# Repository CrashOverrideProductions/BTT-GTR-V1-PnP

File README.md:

# BTT-GTR-V1-PnP  

### **Project**: Pick and Place Expansion Board For BIGTREETECH GTR V1.0

<!-- Repo Cover Image -->

<!-- Repo Stats -->

<!-- Repo Intro -->
### Details
The Goal of this Project is to Create an Expansion Board for the BIGTREETECH 32-Bit 3D Printer Mainboard that includes Functionallity for Pick and Place Machines

<!-- To Do List -->
### Project To Do List
- [X] Design Expansion Board
- [X] Import Marlin
- [X] Import Modified Marlin for PnP (https://github.com/sphawes/index)
- [ ] Create Marlin Board Definition
- [ ] Define RS-485 Communications

### Expansion Board To Do List
- [X] USB Hub
- [X] Vaccuum Sensors
- [X] RS-485
- [ ] More to Add I'm Sure

<!-- Licencing Always at the Bottom -->
### Licencing 

**Creative Commons: Attribution - NonCommercial - ShareAlike 4.0 International (CC BY-NC-SA 4.0)**

**You are free to:**
**Share** — copy and redistribute the material in any medium or format
**Adapt** — remix, transform, and build upon the material

**Under the following terms:**
**Attribution** — You must give appropriate credit, provide a link to the license, and indicate if changes were made. You may do so in any reasonable manner, but not in any way that suggests the licensor endorses you or your use.

**NonCommercial** — You may not use the material for commercial purposes.

**ShareAlike** — If you remix, transform, or build upon the material, you must distribute your contributions under the same license as the original.

No additional restrictions — You may not apply legal terms or technological measures that legally restrict others from doing anything the license permits.

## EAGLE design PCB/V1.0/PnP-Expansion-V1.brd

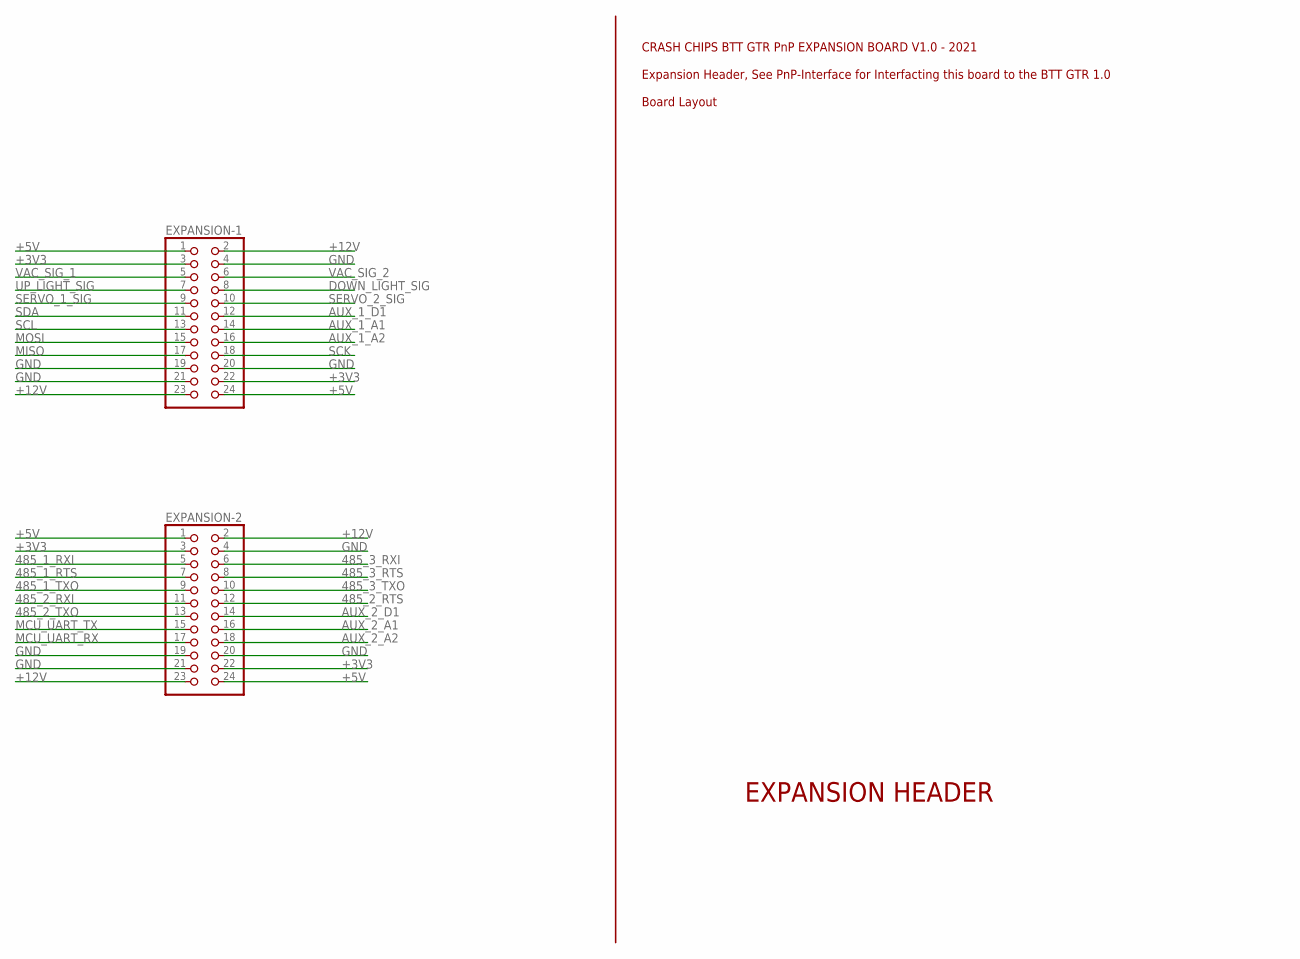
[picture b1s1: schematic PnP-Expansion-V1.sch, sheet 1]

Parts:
EXPANSION-1, EXPANSION-2: PINHD-2X12; 2X12

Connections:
485_1_RTS: EXPANSION-2.7; also elsewhere on the board
485_1_RXI: EXPANSION-2.5; also elsewhere on the board
485_1_TXO: EXPANSION-2.9; also elsewhere on the board
485_2_RTS: EXPANSION-2.12; also elsewhere on the board
485_2_RXI: EXPANSION-2.11; also elsewhere on the board
485_2_TXO: EXPANSION-2.13; also elsewhere on the board
485_3_RTS: EXPANSION-2.8; also elsewhere on the board
485_3_RXI: EXPANSION-2.6; also elsewhere on the board
485_3_TXO: EXPANSION-2.10; also elsewhere on the board
+3V3: EXPANSION-1.3, EXPANSION-1.22, EXPANSION-2.3, EXPANSION-2.22; also elsewhere on the board
+5V: EXPANSION-1.1, EXPANSION-1.24, EXPANSION-2.1, EXPANSION-2.24; also elsewhere on the board
+12V: EXPANSION-1.2, EXPANSION-1.23, EXPANSION-2.2, EXPANSION-2.23; also elsewhere on the board
AUX_1_A1: EXPANSION-1.14; also elsewhere on the board
AUX_1_A2: EXPANSION-1.16; also elsewhere on the board
AUX_1_D1: EXPANSION-1.12; also elsewhere on the board
AUX_2_A1: EXPANSION-2.16; also elsewhere on the board
AUX_2_A2: EXPANSION-2.18; also elsewhere on the board
AUX_2_D1: EXPANSION-2.14; also elsewhere on the board
DOWN_LIGHT_SIG: EXPANSION-1.8; also elsewhere on the board
GND: EXPANSION-1.4, EXPANSION-1.19, EXPANSION-1.20, EXPANSION-1.21, EXPANSION-2.4, EXPANSION-2.19, EXPANSION-2.20, EXPANSION-2.21; also elsewhere on the board
MCU_UART_RX: EXPANSION-2.17; also elsewhere on the board
MCU_UART_TX: EXPANSION-2.15; also elsewhere on the board
MISO: EXPANSION-1.17; also elsewhere on the board
MOSI: EXPANSION-1.15; also elsewhere on the board
SCK: EXPANSION-1.18; also elsewhere on the board
SCL: EXPANSION-1.13; also elsewhere on the board
SDA: EXPANSION-1.11; also elsewhere on the board
SERVO_1_SIG: EXPANSION-1.9; also elsewhere on the board
SERVO_2_SIG: EXPANSION-1.10; also elsewhere on the board
UP_LIGHT_SIG: EXPANSION-1.7; also elsewhere on the board
VAC_SIG_1: EXPANSION-1.5; also elsewhere on the board
VAC_SIG_2: EXPANSION-1.6; also elsewhere on the board

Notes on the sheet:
EXPANSION HEADER
CRASH CHIPS BTT GTR PnP EXPANSION BOARD V1.0 - 2021 Expansion Header, See PnP-Interface for Interfacting this board to the BTT GTR 1.0 Board Layout

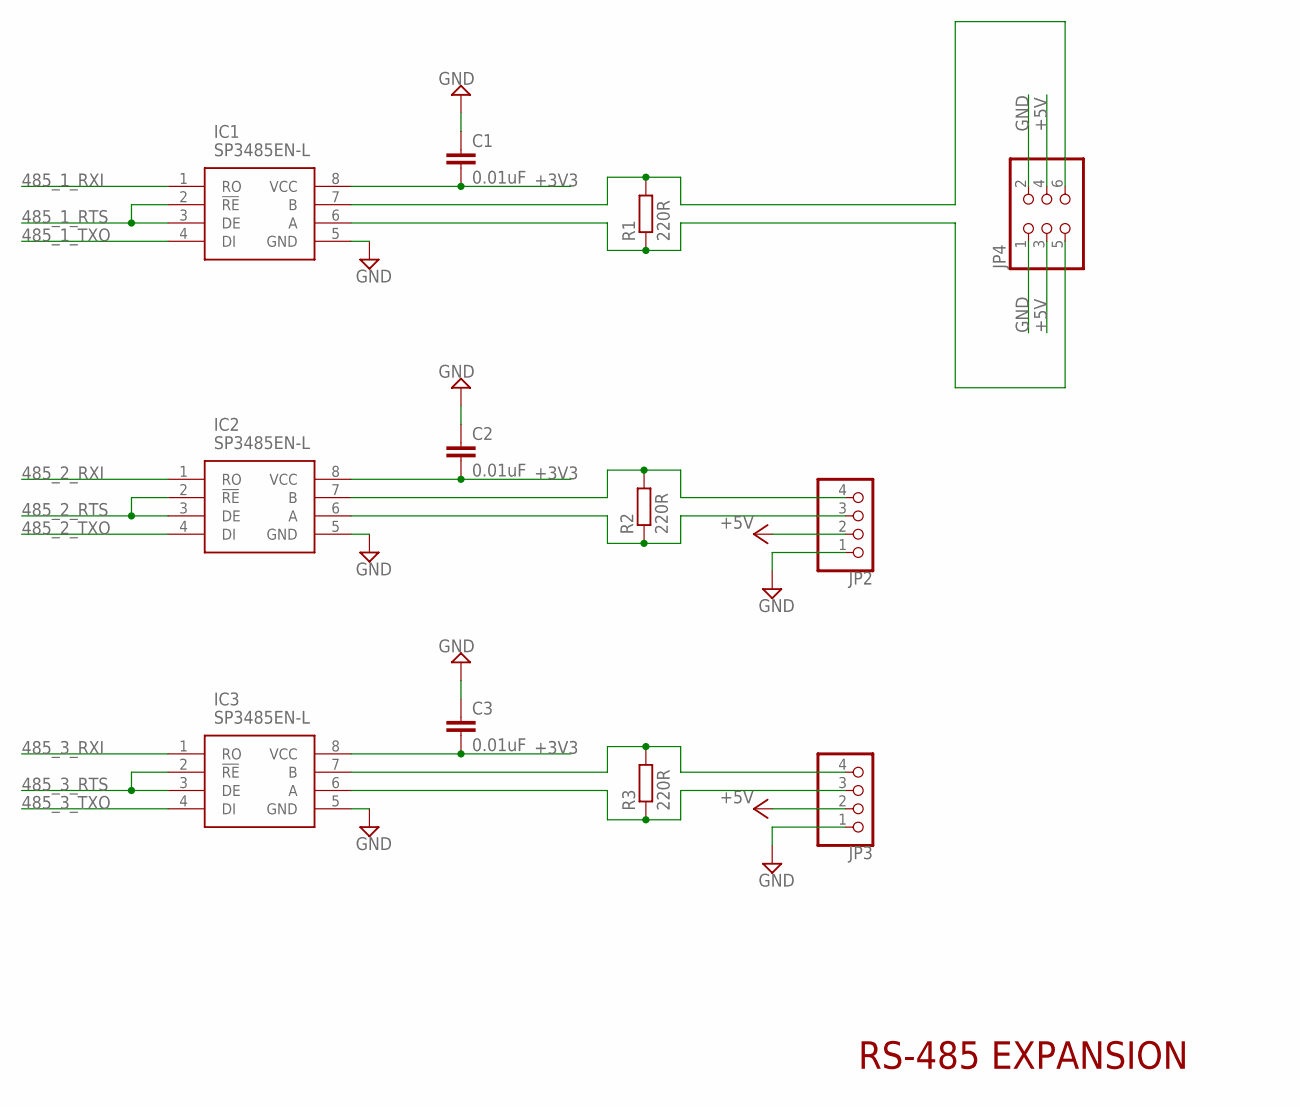
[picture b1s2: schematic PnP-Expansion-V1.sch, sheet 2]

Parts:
C1, C2, C3: 0.01uF; C0805
IC1, IC2, IC3: SP3485EN-L; SOIC127P600X175-8N
JP2, JP3: PINHD-1X4; 1X04
JP4: PINHD-2X3; 2X03
R1, R2, R3: 220R; M0805

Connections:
485_1_RTS: IC1.2 (!RE), IC1.3 (DE); also elsewhere on the board
485_1_RXI: IC1.1 (RO); also elsewhere on the board
485_1_TXO: IC1.4 (DI); also elsewhere on the board
485_2_RTS: IC2.2 (!RE), IC2.3 (DE); also elsewhere on the board
485_2_RXI: IC2.1 (RO); also elsewhere on the board
485_2_TXO: IC2.4 (DI); also elsewhere on the board
485_3_RTS: IC3.2 (!RE), IC3.3 (DE); also elsewhere on the board
485_3_RXI: IC3.1 (RO); also elsewhere on the board
485_3_TXO: IC3.4 (DI); also elsewhere on the board
+3V3: C1.2, C2.2, C3.2, IC1.8 (VCC), IC2.8 (VCC), IC3.8 (VCC); also elsewhere on the board
+5V: JP2.2, JP3.2, JP4.3, JP4.4; also elsewhere on the board
GND: C1.1, C2.1, C3.1, IC1.5 (GND), IC2.5 (GND), IC3.5 (GND), JP2.1, JP3.1, JP4.1, JP4.2; also elsewhere on the board
unnamed: IC3.7 (B), JP3.4, R3.2
unnamed: IC3.6 (A), JP3.3, R3.1
unnamed: IC2.6 (A), JP2.3, R2.1
unnamed: IC2.7 (B), JP2.4, R2.2
unnamed: IC1.6 (A), JP4.5, R1.1
unnamed: IC1.7 (B), JP4.6, R1.2

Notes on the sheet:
RS-485 EXPANSION

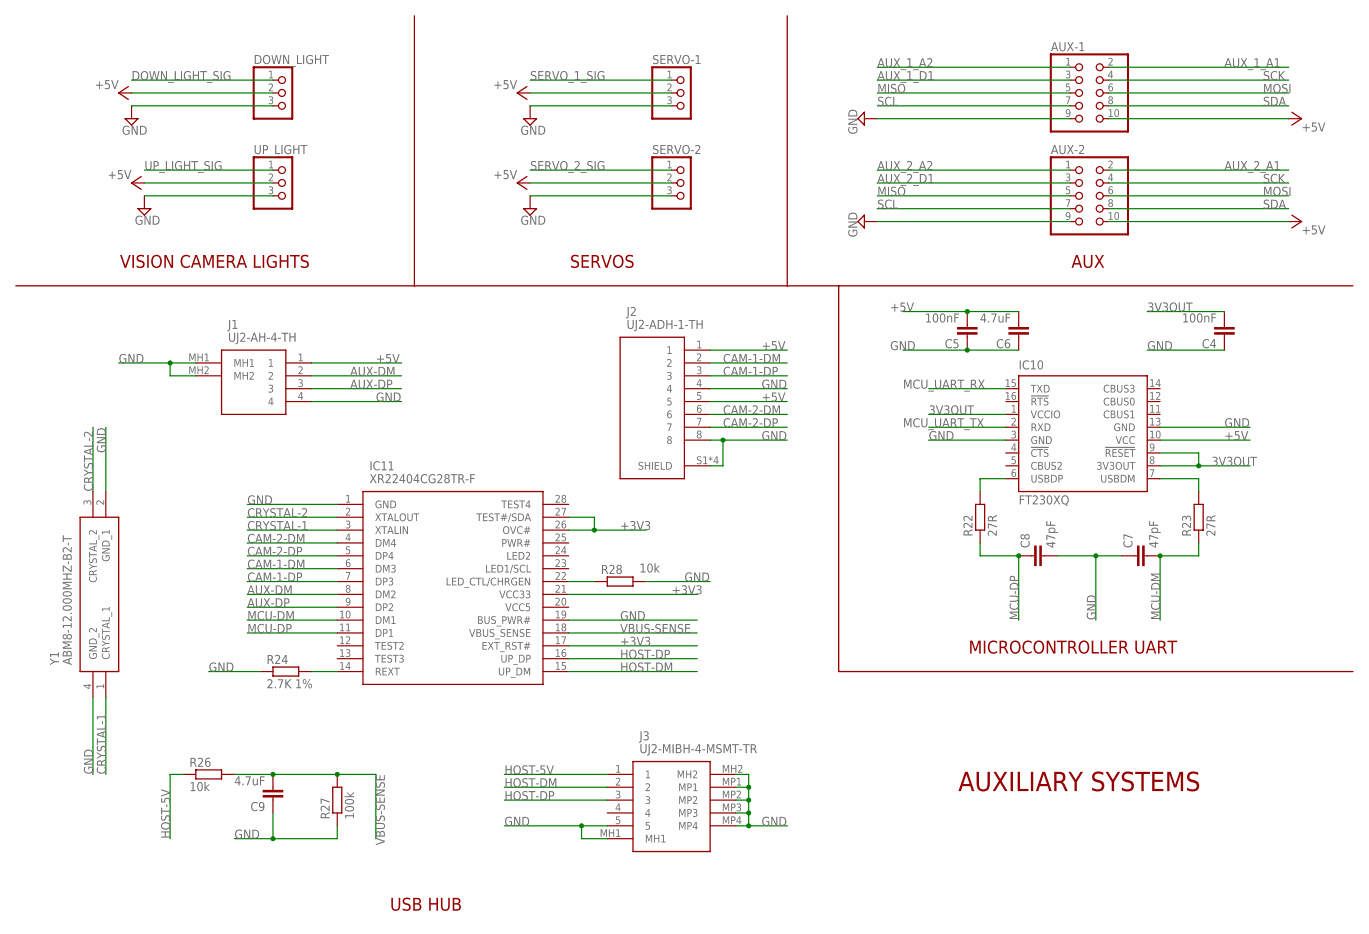
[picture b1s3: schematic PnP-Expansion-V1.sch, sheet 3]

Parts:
AUX-1, AUX-2: PINHD-2X5; 2X05
C4, C5: 100nF; C0805
C6, C9: 4.7uF; C0805
C7, C8: 47pF; C0805
DOWN_LIGHT: PINHD-1X3; 1X03
IC10: FT230XQ; QFN16
IC11: XR22404CG28TR-F; SOP64P600X173-28N
J1: UJ2-AH-4-TH; UJ2AH4TH
J2: UJ2-ADH-1-TH; CUI_UJ2-ADH-1-TH
J3: UJ2-MIBH-4-MSMT-TR; UJ2MIBH4MSMTTR
R22, R23: 27R; M0805
R24: 2.7K 1%; M0805
R26, R28: 10k; M0805
R27: 100k; M0805
SERVO-1, SERVO-2: PINHD-1X3; 1X03
UP_LIGHT: PINHD-1X3; 1X03
Y1: ABM8-12.000MHZ-B2-T; ABM812000MHZB2T

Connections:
3V3OUT: C4.1, IC10.1 (VCCIO), IC10.8 (3V3OUT), IC10.9 (!RESET)
+3V3: IC11.17 (EXT_RST#), IC11.21 (VCC33), IC11.26 (OVC#), IC11.27 (TEST#/SDA); also elsewhere on the board
+5V: AUX-1.10, AUX-2.10, C5.2, C6.2, DOWN_LIGHT.2, IC10.10 (VCC), J1.1, J2.1, J2.5, SERVO-1.2, SERVO-2.2, UP_LIGHT.2; also elsewhere on the board
AUX-DM: IC11.8 (DM2), J1.2
AUX-DP: IC11.9 (DP2), J1.3
AUX_1_A1: AUX-1.2; also elsewhere on the board
AUX_1_A2: AUX-1.1; also elsewhere on the board
AUX_1_D1: AUX-1.3; also elsewhere on the board
AUX_2_A1: AUX-2.2; also elsewhere on the board
AUX_2_A2: AUX-2.1; also elsewhere on the board
AUX_2_D1: AUX-2.3; also elsewhere on the board
CAM-1-DM: IC11.6 (DM3), J2.2
CAM-1-DP: IC11.7 (DP3), J2.3
CAM-2-DM: IC11.4 (DM4), J2.6
CAM-2-DP: IC11.5 (DP4), J2.7
CRYSTAL-1: IC11.3 (XTALIN), Y1.1 (CRYSTAL_1)
CRYSTAL-2: IC11.2 (XTALOUT), Y1.3 (CRYSTAL_2)
DOWN_LIGHT_SIG: DOWN_LIGHT.1; also elsewhere on the board
GND: AUX-1.9, AUX-2.9, C4.2, C5.1, C6.1, C7.1, C8.2, C9.1, DOWN_LIGHT.3, IC10.3 (GND), IC10.13 (GND), IC11.1 (GND), IC11.19 (BUS_PWR#), J1.4, J1.MH1, J1.MH2, J2.4, J2.8, J2.S1 (SHIELD), J2.S2 (SHIELD), J2.S3 (SHIELD), J2.S4 (SHIELD), J3.5, J3.MH1, J3.MH2, J3.MP1, J3.MP2, J3.MP3, J3.MP4, R24.1, R27.1, R28.2, SERVO-1.3, SERVO-2.3, UP_LIGHT.3, Y1.2 (GND_1), Y1.4 (GND_2); also elsewhere on the board
HOST-5V: J3.1, R26.1
HOST-DM: IC11.15 (UP_DM), J3.2
HOST-DP: IC11.16 (UP_DP), J3.3
MCU-DM: C7.2, IC11.10 (DM1), R23.1
MCU-DP: C8.1, IC11.11 (DP1), R22.1
MCU_UART_RX: IC10.15 (TXD); also elsewhere on the board
MCU_UART_TX: IC10.2 (RXD); also elsewhere on the board
MISO: AUX-1.5, AUX-2.5; also elsewhere on the board
MOSI: AUX-1.6, AUX-2.6; also elsewhere on the board
unnamed: IC11.22 (LED_CTL/CHRGEN), R28.1
unnamed: IC10.6 (USBDP), R22.2
unnamed: IC10.7 (USBDM), R23.2
unnamed: IC11.14 (REXT), R24.2
SCK: AUX-1.4, AUX-2.4; also elsewhere on the board
SCL: AUX-1.7, AUX-2.7; also elsewhere on the board
SDA: AUX-1.8, AUX-2.8; also elsewhere on the board
SERVO_1_SIG: SERVO-1.1; also elsewhere on the board
SERVO_2_SIG: SERVO-2.1; also elsewhere on the board
UP_LIGHT_SIG: UP_LIGHT.1; also elsewhere on the board
VBUS-SENSE: C9.2, IC11.18 (VBUS_SENSE), R26.2, R27.2

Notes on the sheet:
AUXILIARY SYSTEMS
VISION CAMERA LIGHTS
SERVOS
AUX
MICROCONTROLLER UART
USB HUB

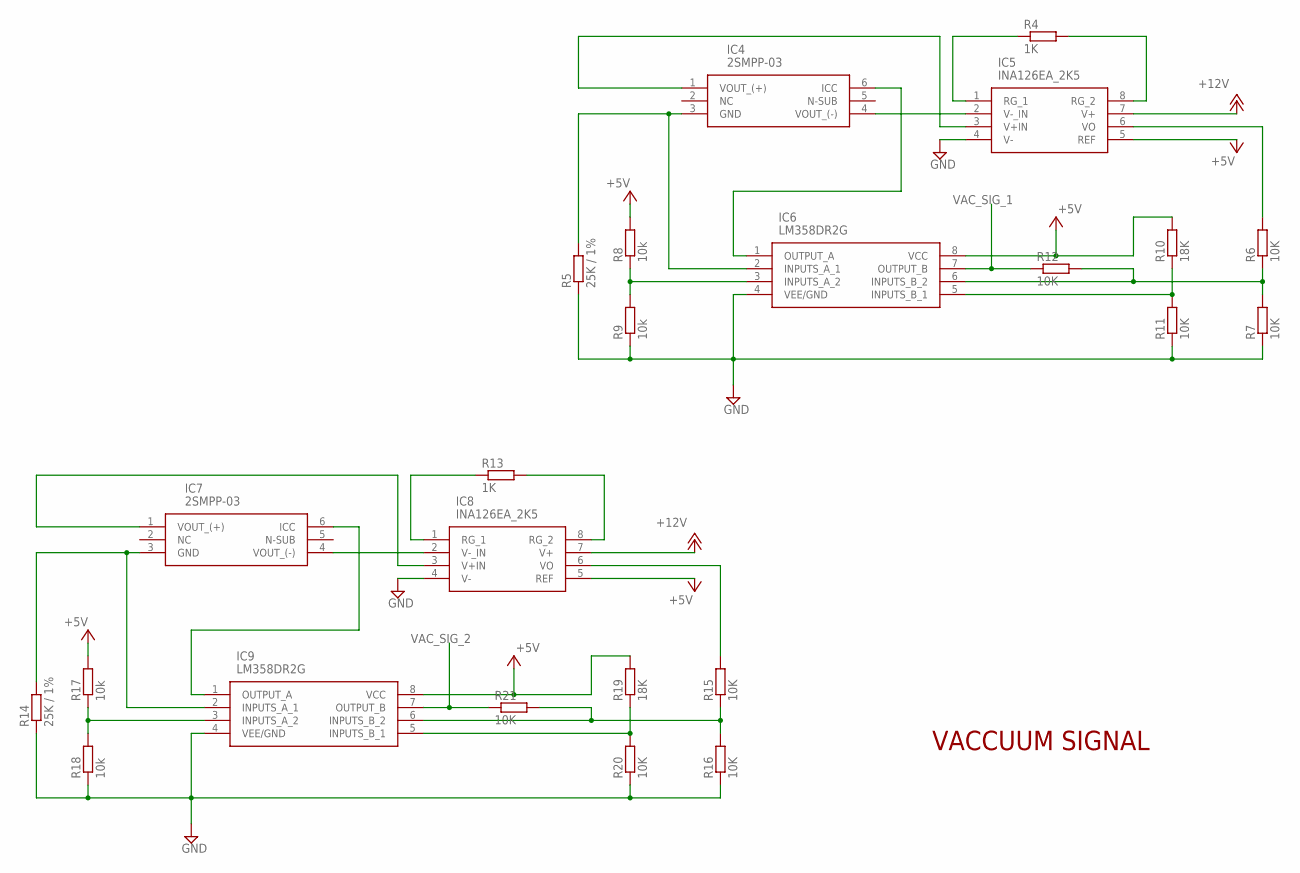
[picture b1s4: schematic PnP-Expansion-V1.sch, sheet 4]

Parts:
IC4, IC7: 2SMPP-03; 2SMPP03
IC5, IC8: INA126EA_2K5; SOP65P490X110-8N
IC6, IC9: LM358DR2G; SOIC127P600X175-8N
R4, R13: 1K; M0805
R5, R14: 25K / 1%; M0805
R6, R7, R11, R12, R15, R16, R20, R21: 10K; M0805
R8, R9, R17, R18: 10k; M0805
R10, R19: 18K; M0805

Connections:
+5V: IC5.5 (REF), IC6.8 (VCC), IC8.5 (REF), IC9.8 (VCC), R8.2, R10.2, R17.2, R19.2; also elsewhere on the board
+12V: IC5.7 (V+), IC8.7 (V+); also elsewhere on the board
GND: IC5.4 (V-), IC6.4 (VEE/GND), IC8.4 (V-), IC9.4 (VEE/GND), R5.1, R7.1, R9.1, R11.1, R14.1, R16.1, R18.1, R20.1; also elsewhere on the board
unnamed: IC4.1 (VOUT_(+)), IC5.3 (V+IN)
unnamed: IC5.1 (RG_1), R4.1
unnamed: IC5.8 (RG_2), R4.2
unnamed: IC4.4 (VOUT_(-)), IC5.2 (V-_IN)
unnamed: IC4.6 (ICC), IC6.1 (OUTPUT_A)
unnamed: IC4.3 (GND), IC6.2 (INPUTS_A_1), R5.2
unnamed: IC6.3 (INPUTS_A_2), R8.1, R9.2
unnamed: IC5.6 (VO), R6.2
unnamed: IC6.6 (INPUTS_B_2), R6.1, R7.2, R12.2
unnamed: IC6.5 (INPUTS_B_1), R10.1, R11.2
unnamed: IC7.1 (VOUT_(+)), IC8.3 (V+IN)
unnamed: IC8.1 (RG_1), R13.1
unnamed: IC8.8 (RG_2), R13.2
unnamed: IC7.4 (VOUT_(-)), IC8.2 (V-_IN)
unnamed: IC7.6 (ICC), IC9.1 (OUTPUT_A)
unnamed: IC7.3 (GND), IC9.2 (INPUTS_A_1), R14.2
unnamed: IC9.3 (INPUTS_A_2), R17.1, R18.2
unnamed: IC8.6 (VO), R15.2
unnamed: IC9.6 (INPUTS_B_2), R15.1, R16.2, R21.2
unnamed: IC9.5 (INPUTS_B_1), R19.1, R20.2
VAC_SIG_1: IC6.7 (OUTPUT_B), R12.1; also elsewhere on the board
VAC_SIG_2: IC9.7 (OUTPUT_B), R21.1; also elsewhere on the board

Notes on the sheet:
VACCUUM SIGNAL

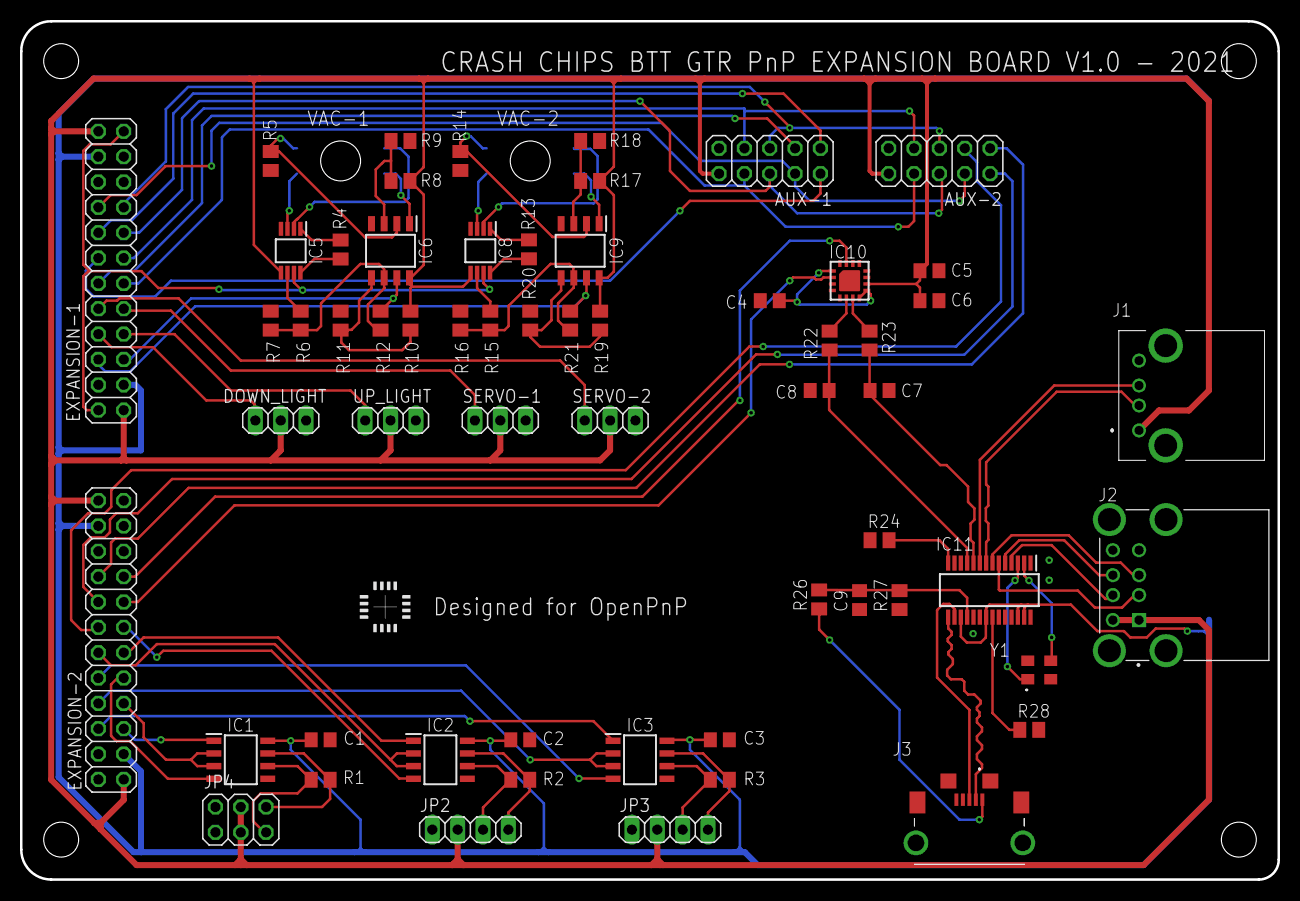
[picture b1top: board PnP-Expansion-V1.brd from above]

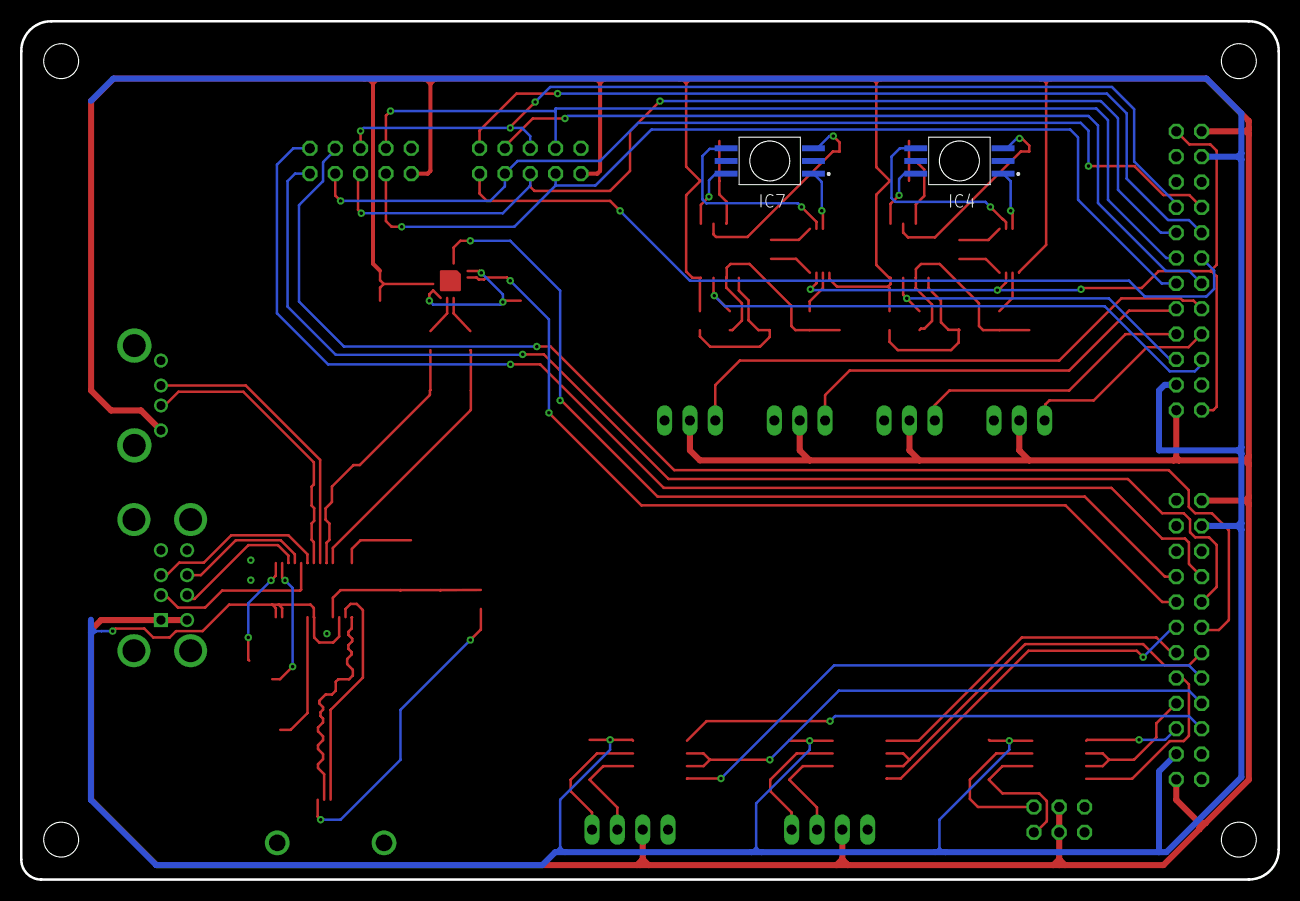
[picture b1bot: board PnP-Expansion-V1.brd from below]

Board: 2 copper layers, 126.0 x 86.0 mm, 62 parts (2 on the bottom side), 77 nets.

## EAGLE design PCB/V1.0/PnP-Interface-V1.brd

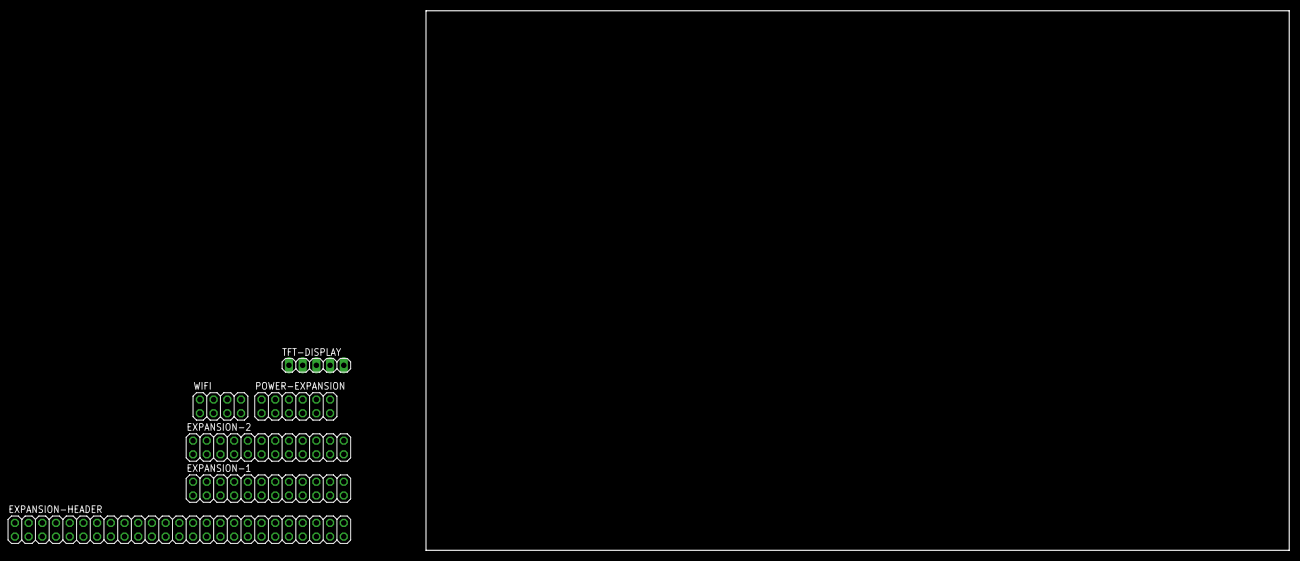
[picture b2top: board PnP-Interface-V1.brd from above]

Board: 2 copper layers, 160.0 x 100.0 mm, 6 parts (0 on the bottom side), 14 nets, no tracks yet.

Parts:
EXPANSION-1, EXPANSION-2: 2X12
EXPANSION-HEADER: 2X25
POWER-EXPANSION: 2X06
TFT-DISPLAY: 1X05
WIFI: 2X04

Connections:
485_1_RTS: EXPANSION-2.7, EXPANSION-HEADER.28
485_1_RXI: EXPANSION-2.5, TFT-DISPLAY.3
485_1_TXO: EXPANSION-2.9, TFT-DISPLAY.2
+3V3: EXPANSION-1.3, EXPANSION-1.22, EXPANSION-2.3, EXPANSION-2.22, POWER-EXPANSION.1, POWER-EXPANSION.3, WIFI.7
+5V: EXPANSION-1.1, EXPANSION-1.24, EXPANSION-2.1, EXPANSION-2.24, POWER-EXPANSION.5, POWER-EXPANSION.7, TFT-DISPLAY.5
+12V: EXPANSION-1.2, EXPANSION-1.23, EXPANSION-2.2, EXPANSION-2.23, POWER-EXPANSION.9, POWER-EXPANSION.11
DOWN_LIGHT_SIG: EXPANSION-1.8, EXPANSION-HEADER.20
GND: EXPANSION-1.4, EXPANSION-1.19, EXPANSION-1.20, EXPANSION-1.21, EXPANSION-2.4, EXPANSION-2.19, EXPANSION-2.20, EXPANSION-2.21, EXPANSION-HEADER.1, POWER-EXPANSION.2, POWER-EXPANSION.4, POWER-EXPANSION.6, POWER-EXPANSION.8, POWER-EXPANSION.10, POWER-EXPANSION.12, TFT-DISPLAY.4, WIFI.2
MCU_UART_RX: EXPANSION-2.17, WIFI.1, WIFI.8
SERVO_1_SIG: EXPANSION-1.9, EXPANSION-HEADER.25
SERVO_2_SIG: EXPANSION-1.10, EXPANSION-HEADER.27
UP_LIGHT_SIG: EXPANSION-1.7, EXPANSION-HEADER.23
VAC_SIG_1: EXPANSION-1.5, EXPANSION-HEADER.46
VAC_SIG_2: EXPANSION-1.6, EXPANSION-HEADER.43

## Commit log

2021-02-11 start of research files
2021-02-12 marlin upload
2021-02-12 start planning
2021-02-27 Restructure
2021-02-27 v1 update

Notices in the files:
README.md:
License: CC-BY-NC-SA-4.0
